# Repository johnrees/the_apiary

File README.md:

## Overview

My Fab Academy Final Project.

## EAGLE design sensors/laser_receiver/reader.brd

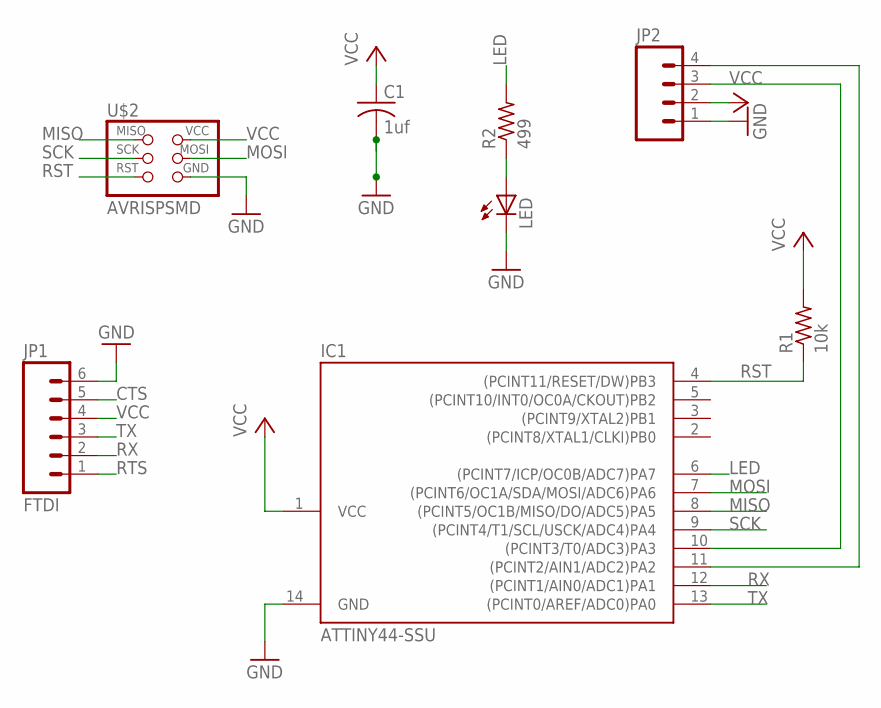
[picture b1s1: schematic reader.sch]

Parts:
C1: 1uf; C1206
IC1: ATTINY44-SSU; SOIC14
JP1: FTDI; 1X06-SMD
JP2: M04LONGPADS; 1X04_LONGPADS
LED: LEDSMT1206; 1206
R1: 10k; R1206
R2: 499; R1206
U$2: AVRISPSMD; 2X03SMD

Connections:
CTS: JP1.5
GND: C1.2, IC1.14 (GND), JP1.6, JP2.1, LED.C, U$2.6 (GND)
LED: IC1.6 ((PCINT7/ICP/OC0B/ADC7)PA7), R2.2
MISO: IC1.8 ((PCINT5/OC1B/MISO/DO/ADC5)PA5), U$2.1 (MISO)
MOSI: IC1.7 ((PCINT6/OC1A/SDA/MOSI/ADC6)PA6), U$2.4 (MOSI)
unnamed: IC1.10 ((PCINT3/T0/ADC3)PA3), JP2.3
unnamed: IC1.11 ((PCINT2/AIN1/ADC2)PA2), JP2.4
unnamed: LED.A, R2.1
RST: IC1.4 ((PCINT11/RESET/DW)PB3), R1.1, U$2.5 (RST)
RTS: JP1.1
RX: IC1.12 ((PCINT1/AIN0/ADC1)PA1), JP1.2
SCK: IC1.9 ((PCINT4/T1/SCL/USCK/ADC4)PA4), U$2.3 (SCK)
TX: IC1.13 ((PCINT0/AREF/ADC0)PA0), JP1.3
VCC: C1.1, IC1.1 (VCC), JP1.4, JP2.2, R1.2, U$2.2 (VCC)

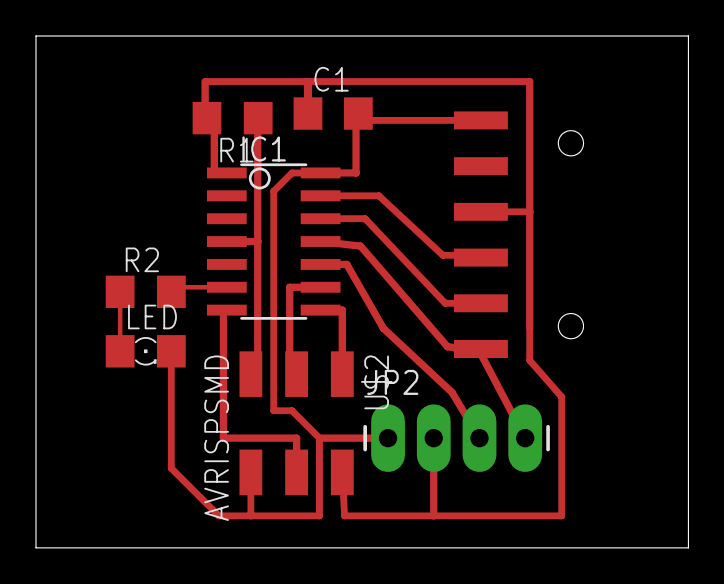
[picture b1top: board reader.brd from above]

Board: 1 copper layer, 36.2 x 28.4 mm, 8 parts (0 on the bottom side), 12 nets.

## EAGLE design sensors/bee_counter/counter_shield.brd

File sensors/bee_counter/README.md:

# Bee Counter

Based on http://www.instructables.com/id/Honey-Bee-Counter/

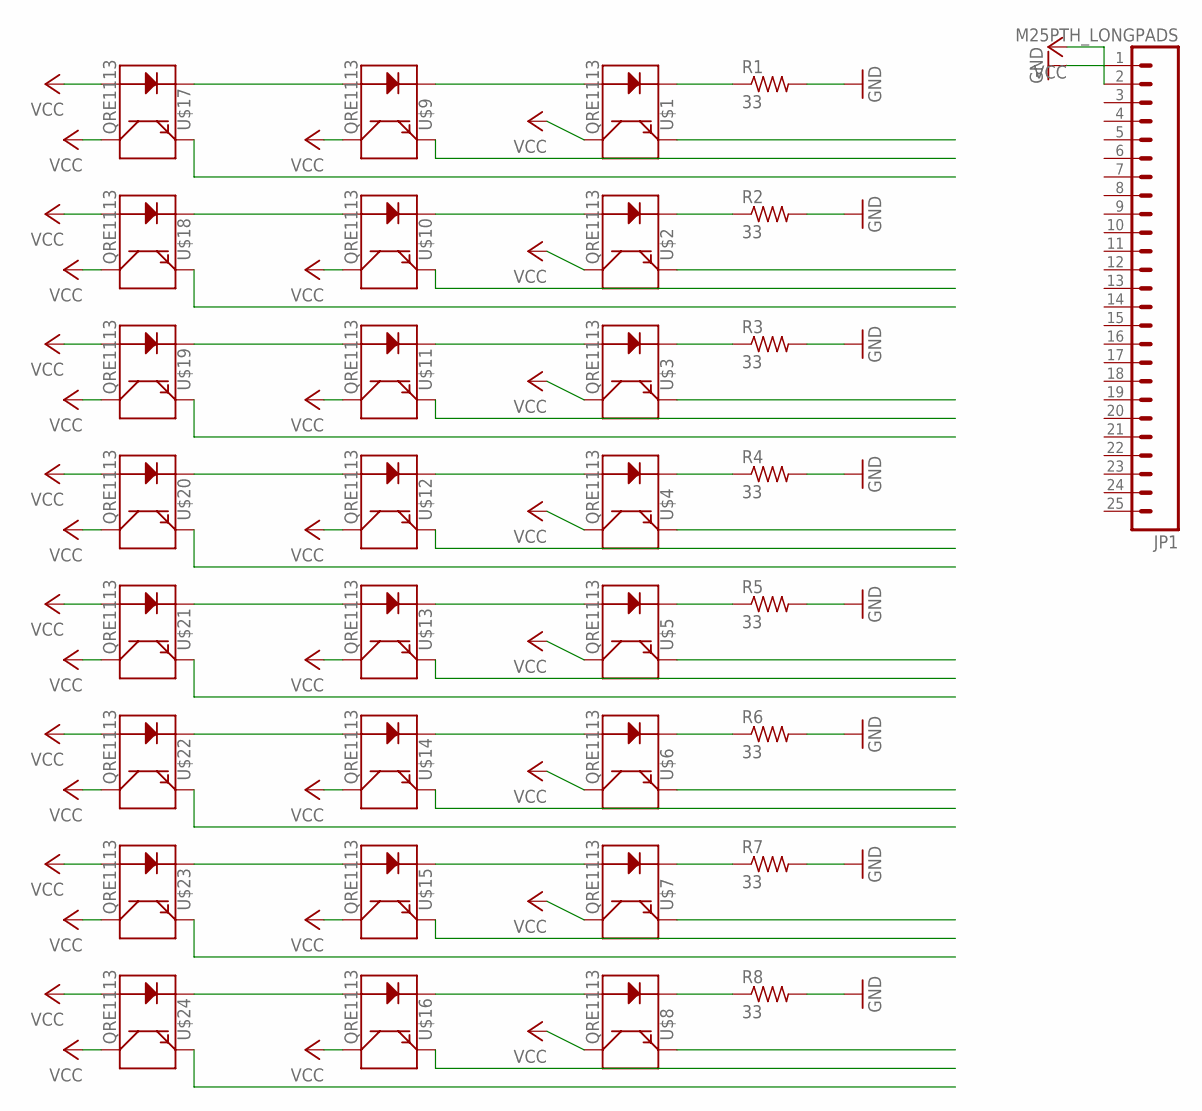
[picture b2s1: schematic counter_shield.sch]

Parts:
JP1: M25PTH_LONGPADS; 1X25_LONGPAD
R1, R2, R3, R4, R5, R6, R7, R8: 33; 1206
U$1, U$2, U$3, U$4, U$5, U$6, U$7, U$8, U$9, U$10, U$11, U$12, U$13, U$14, U$15, U$16, U$17, U$18, U$19, U$20, U$21, U$22, U$23, U$24: QRE1113

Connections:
GND: JP1.2, R1.2, R2.2, R3.2, R4.2, R5.2, R6.2, R7.2, R8.2
unnamed: U$9.1 (A), U$17.2 (K)
unnamed: U$1.1 (A), U$9.2 (K)
unnamed: U$10.1 (A), U$18.2 (K)
unnamed: U$2.1 (A), U$10.2 (K)
unnamed: U$3.1 (A), U$11.2 (K)
unnamed: U$11.1 (A), U$19.2 (K)
unnamed: U$12.1 (A), U$20.2 (K)
unnamed: U$4.1 (A), U$12.2 (K)
unnamed: U$13.1 (A), U$21.2 (K)
unnamed: U$5.1 (A), U$13.2 (K)
unnamed: U$6.1 (A), U$14.2 (K)
unnamed: U$14.1 (A), U$22.2 (K)
unnamed: U$15.1 (A), U$23.2 (K)
unnamed: U$7.1 (A), U$15.2 (K)
unnamed: U$8.1 (A), U$16.2 (K)
unnamed: U$16.1 (A), U$24.2 (K)
unnamed: R8.1, U$8.2 (K)
unnamed: R7.1, U$7.2 (K)
unnamed: R6.1, U$6.2 (K)
unnamed: R5.1, U$5.2 (K)
unnamed: R4.1, U$4.2 (K)
unnamed: R3.1, U$3.2 (K)
unnamed: R2.1, U$2.2 (K)
unnamed: R1.1, U$1.2 (K)
VCC: JP1.1, U$1.3 (C), U$2.3 (C), U$3.3 (C), U$4.3 (C), U$5.3 (C), U$6.3 (C), U$7.3 (C), U$8.3 (C), U$9.3 (C), U$10.3 (C), U$11.3 (C), U$12.3 (C), U$13.3 (C), U$14.3 (C), U$15.3 (C), U$16.3 (C), U$17.1 (A), U$17.3 (C), U$18.1 (A), U$18.3 (C), U$19.1 (A), U$19.3 (C), U$20.1 (A), U$20.3 (C), U$21.1 (A), U$21.3 (C), U$22.1 (A), U$22.3 (C), U$23.1 (A), U$23.3 (C), U$24.1 (A), U$24.3 (C)

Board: 2 copper layers, 33 parts (0 on the bottom side), 26 nets, no tracks yet.

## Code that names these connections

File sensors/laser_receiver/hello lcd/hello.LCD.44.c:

//
// hello.LCD.44.c
//
// LCD hello-world
//
// set lfuse to 0x7E for 20 MHz xtal
//
// Neil Gershenfeld
// 11/14/10
//
// (c) Massachusetts Institute of Technology 2010
// Permission granted for experimental and personal use;
// license for commercial sale available from MIT.
//

#include <avr/io.h>
#include <util/delay.h>
#include <avr/pgmspace.h>

#define output(directions,pin) (directions |= pin) // set port direction for output
#define set(port,pin) (port |= pin) // set port pin
#define clear(port,pin) (port &= (~pin)) // clear port pin
#define pin_test(pins,pin) (pins & pin) // test for port pin
#define bit_test(byte,bit) (byte & (1 << bit)) // test for bit set

#define LCD_port PORTA
#define LCD_direction DDRA
#define DB7 (1 << PA0)
#define DB6 (1 << PA1)
#define DB5 (1 << PA2)
#define DB4 (1 << PA3)
#define E (1 << PA4)
#define RS (1 << PA5)

#define long_delay() _delay_ms(1000) // delay before redraw
#define lcd_delay() _delay_ms(10) // delay between commands
#define strobe_delay() _delay_us(1) // delay for strobe

//
// lcd_putchar
//    put character in lcdbyte
//
void lcd_putchar(char lcdbyte) {
   //
   // set RS for data
   //
   set(LCD_port, RS);
   //
   // output high nibble
   //
   if bit_test(lcdbyte, 7)
      set(LCD_port, DB7);
   else
      clear(LCD_port, DB7);
   if bit_test(lcdbyte, 6)
      set(LCD_port, DB6);
   else
      clear(LCD_port, DB6);
   if bit_test(lcdbyte, 5)
      set(LCD_port, DB5);
   else
      clear(LCD_port, DB5);
   if bit_test(lcdbyte, 4)
      set(LCD_port, DB4);
   else
      clear(LCD_port, DB4);
   //
   // strobe E
   //
   strobe_delay();
   set(LCD_port, E);
   strobe_delay();
   clear(LCD_port, E);
   //
   // wait
   //
   lcd_delay();
   //
   // output low nibble
   //
   if bit_test(lcdbyte, 3)
      set(LCD_port, DB7);
   else
      clear(LCD_port, DB7);
   if bit_test(lcdbyte, 2)
      set(LCD_port, DB6);
   else
      clear(LCD_port, DB6);
   if bit_test(lcdbyte, 1)
      set(LCD_port, DB5);
   else
      clear(LCD_port, DB5);
   if bit_test(lcdbyte, 0)
      set(LCD_port, DB4);
   else
      clear(LCD_port, DB4);
   //
   // strobe E
   //
   strobe_delay();
   set(LCD_port, E);
   strobe_delay();
   clear(LCD_port, E);
   //
   // wait and return
   //
   lcd_delay();
   }
//
// lcd_putcmd
//    put command in lcdbyte
//
void lcd_putcmd(char lcdbyte) {
   //
   // clear RS for command
   //
   clear(LCD_port, RS);
   //
   // output command bits
   //
   PORTA = lcdbyte;
   //
   // strobe E
   //
   strobe_delay();
   set(LCD_port, E);
   strobe_delay();
   clear(LCD_port, E);
   //
   // wait and return
   //
   lcd_delay();
   }
//
// lcd_putstring
//    put a null-terminated string in flash
//
void lcd_putstring(PGM_P message) {
   static uint8_t index;
   static char chr;
   index = 0;
   while (1) {
      chr = pgm_read_byte(&(message[index]));
      if (chr == 0)
         return;
      lcd_putchar(chr);
      ++index;
      }
   }
//
// lcd_init
//    initialize the LCD
//
void lcd_init() {
   //
   // power-up delay
   //
   lcd_delay();
   //
   // initialization sequence
   //
   lcd_putcmd(DB5+DB4);
   lcd_putcmd(DB5+DB4);
   lcd_putcmd(DB5+DB4);
   //
   // 4-bit interface
   //
   lcd_putcmd(DB5);
   //
   // two lines, 5x7 font
   //
   lcd_putcmd(DB5);
   lcd_putcmd(DB7);
   //
   // display on
   //
   lcd_putcmd(0);
   lcd_putcmd(DB7+DB6+DB5);
   //
   // entry mode
   //
   lcd_putcmd(0);
   lcd_putcmd(DB6+DB5);
   }

int main(void) {
   //
   // main
   //
   // set clock divider to /1
   //
   CLKPR = (1 << CLKPCE);
   CLKPR = (0 << CLKPS3) | (0 << CLKPS2) | (0 << CLKPS1) | (0 << CLKPS0);
   //
   // initialize LCD pins
   //
   clear(LCD_port, DB7);
   output(LCD_direction, DB7);
   clear(LCD_port, DB6);
   output(LCD_direction, DB6);
   clear(LCD_port, DB5);
   output(LCD_direction, DB5);
   clear(LCD_port, DB4);
   output(LCD_direction, DB4);
   clear(LCD_port, E);
   output(LCD_direction, E);
   clear(LCD_port, RS);
   output(LCD_direction, RS);
   //
   // initialize LCD
   //
   lcd_init();
   //
   // main loop
   //
   while (1) {
      //
      // go to zero position
      //
      lcd_putcmd(0);
      lcd_putcmd(DB5);
      //
      // print first line from flash
      //
      static const char line1[] PROGMEM = "Hello to";
      lcd_putstring((PGM_P) line1);
      //
      // move to second line
      //
      lcd_putcmd(DB7+DB6);
      lcd_putcmd(0);
      //
      // print second line from flash
      //
      static const char line2[] PROGMEM = "the world";
      lcd_putstring((PGM_P) line2);
      //
      // pause
      //
      long_delay();
      //
      // clear display
      //
      lcd_putcmd(0);
      lcd_putcmd(DB4);
      }
   }

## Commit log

2013-05-26 entrance gates
2013-05-26 counter README
2013-05-26 EAGLE files added
2013-05-26 mini readme
2013-05-27 logo
2013-05-30 hive and counter shield
2013-05-30 laser stuff
2013-07-01 serial test

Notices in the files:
parts and their libraries:
SparkFun-Sensors: Licensing: CC v3.0 Share-Alike You are welcome to use this library for commercial purposes.
